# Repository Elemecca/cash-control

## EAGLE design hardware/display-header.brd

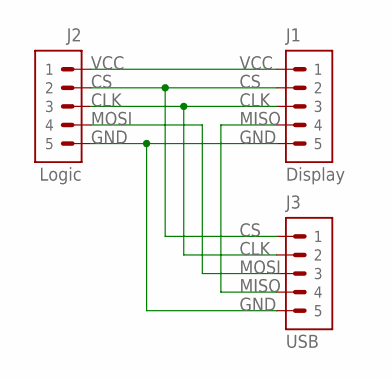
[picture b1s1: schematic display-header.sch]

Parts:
J1: Display; 89400-0520
J2: Logic; 89400-0520
J3: USB; 89400-0520

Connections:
CLK: J1.3, J2.3, J3.2
CS: J1.2, J2.2, J3.1
GND: J1.5, J2.5, J3.5
MISO: J1.4, J3.4
MOSI: J2.4, J3.3
VCC: J1.1, J2.1

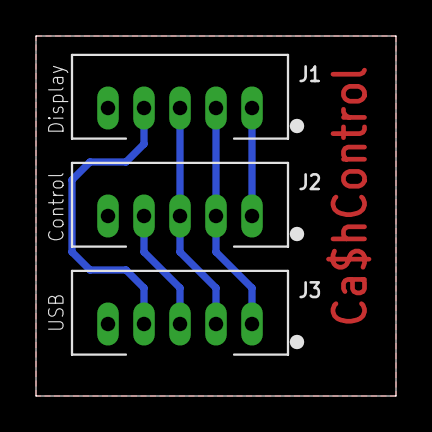
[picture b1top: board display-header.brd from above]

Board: 2 copper layers, 20.0 x 20.0 mm, 3 parts (0 on the bottom side), 6 nets.

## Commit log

2016-01-23 Start project with basic CMake toolchain.
2016-01-23 Add EagleCAD project with first display tap board rev.
2016-06-14 Get the XC16 toolchain working properly.
2016-06-14 Get a basic hello world app running.
2016-06-14 Set up basic USB support with M-Stack.
2016-06-15 Clean up config words.
    This should get more pins working for IO.
2016-06-15 Set up SPI1 to monitor the display bus.
2016-06-16 Break out subsystems into separate files.
2016-06-16 Detect SPI slave select framing.
2016-06-16 Move CMake modules to a separate repo.
2016-06-18 Update cmake-microchip.
